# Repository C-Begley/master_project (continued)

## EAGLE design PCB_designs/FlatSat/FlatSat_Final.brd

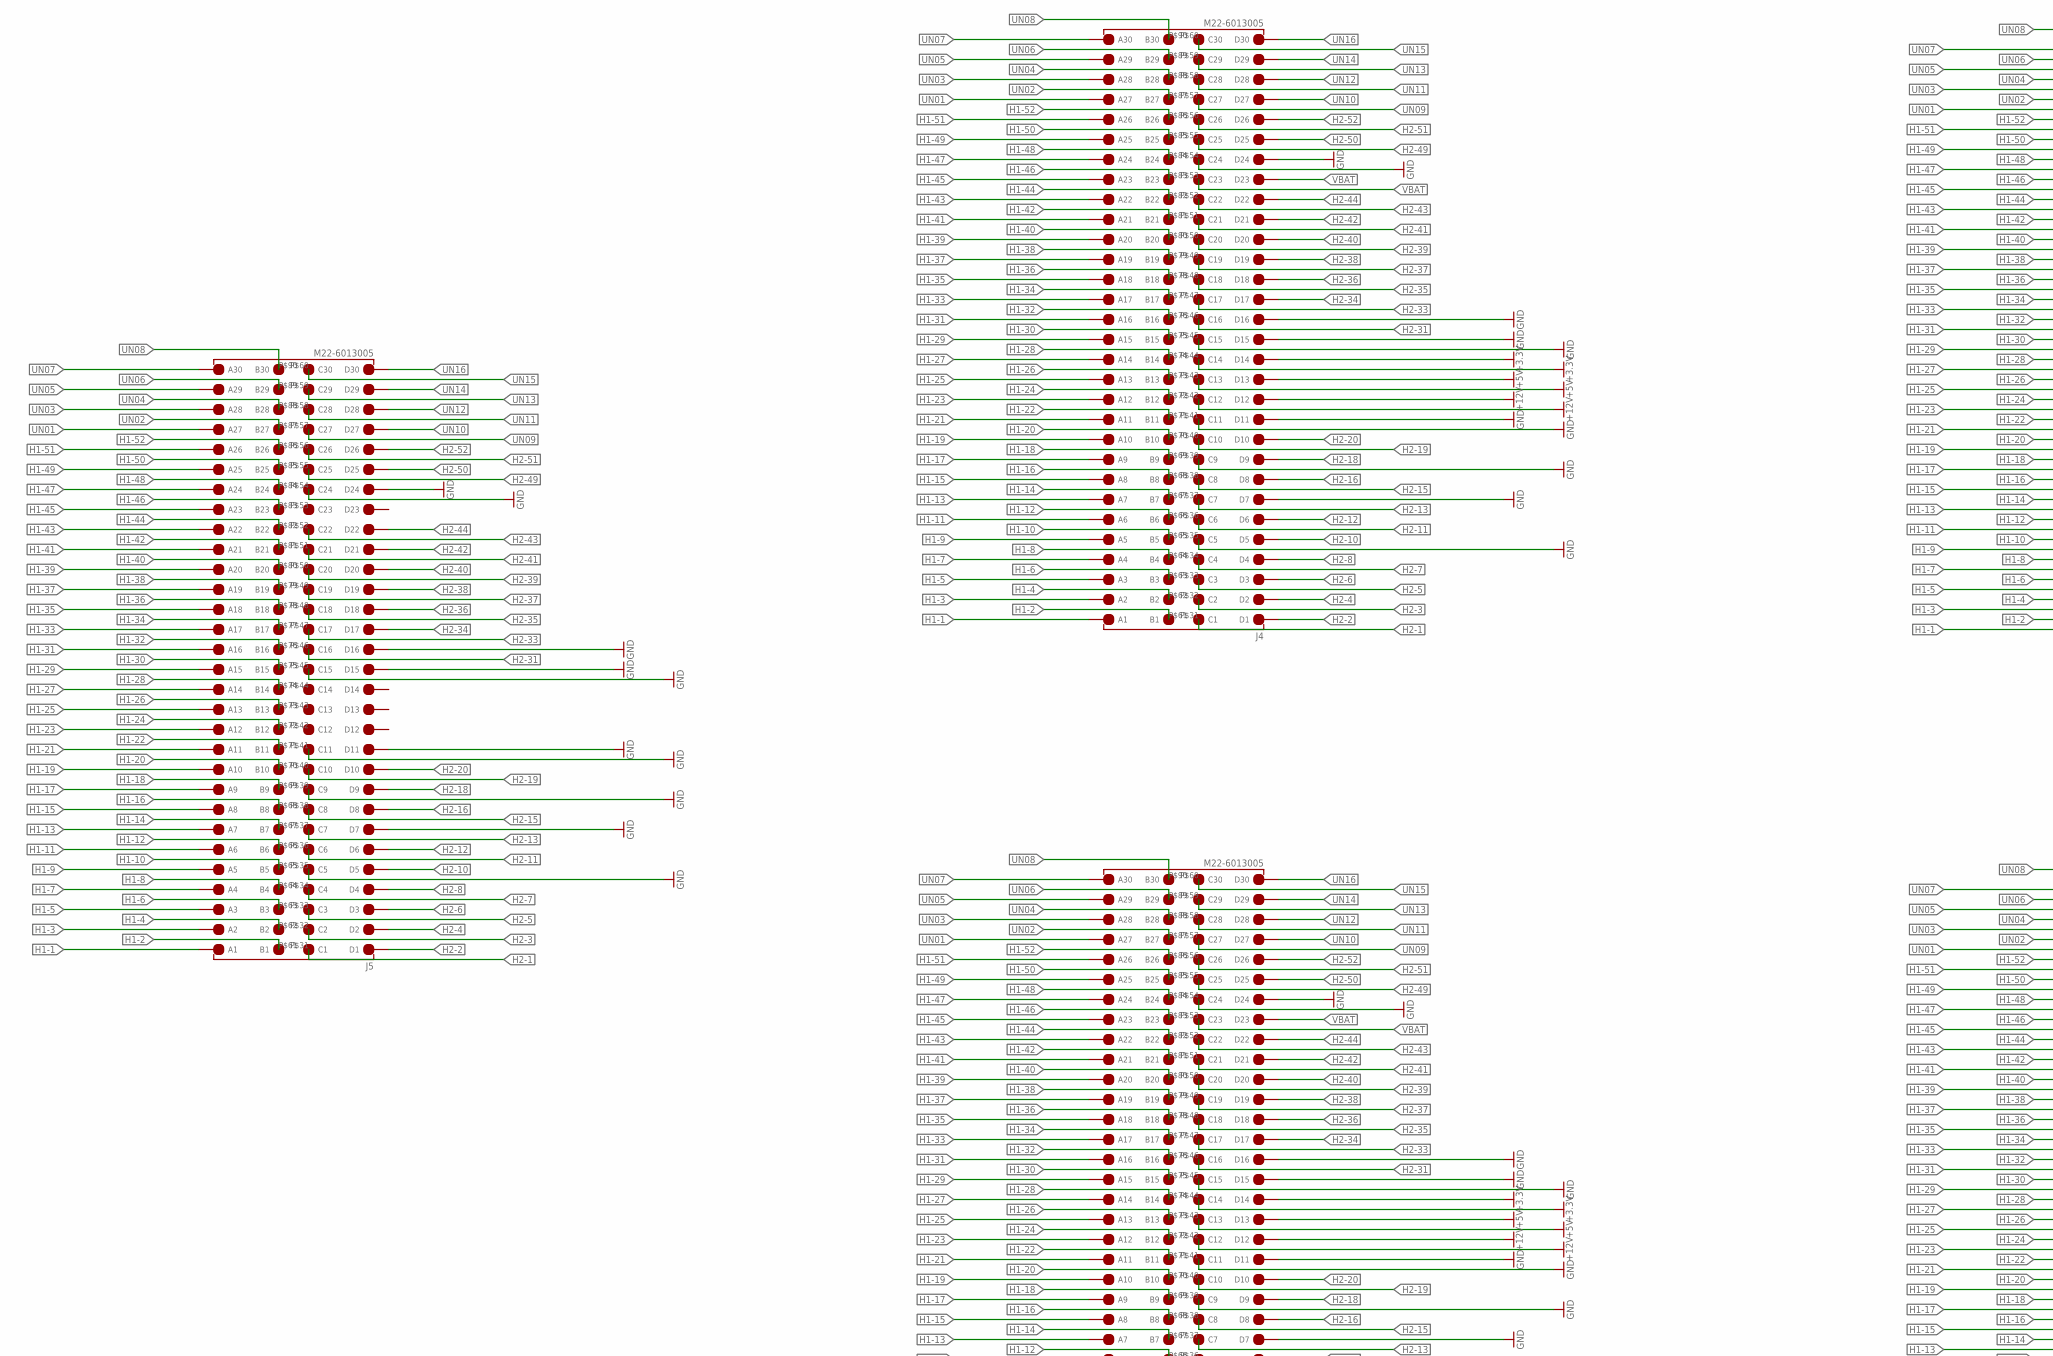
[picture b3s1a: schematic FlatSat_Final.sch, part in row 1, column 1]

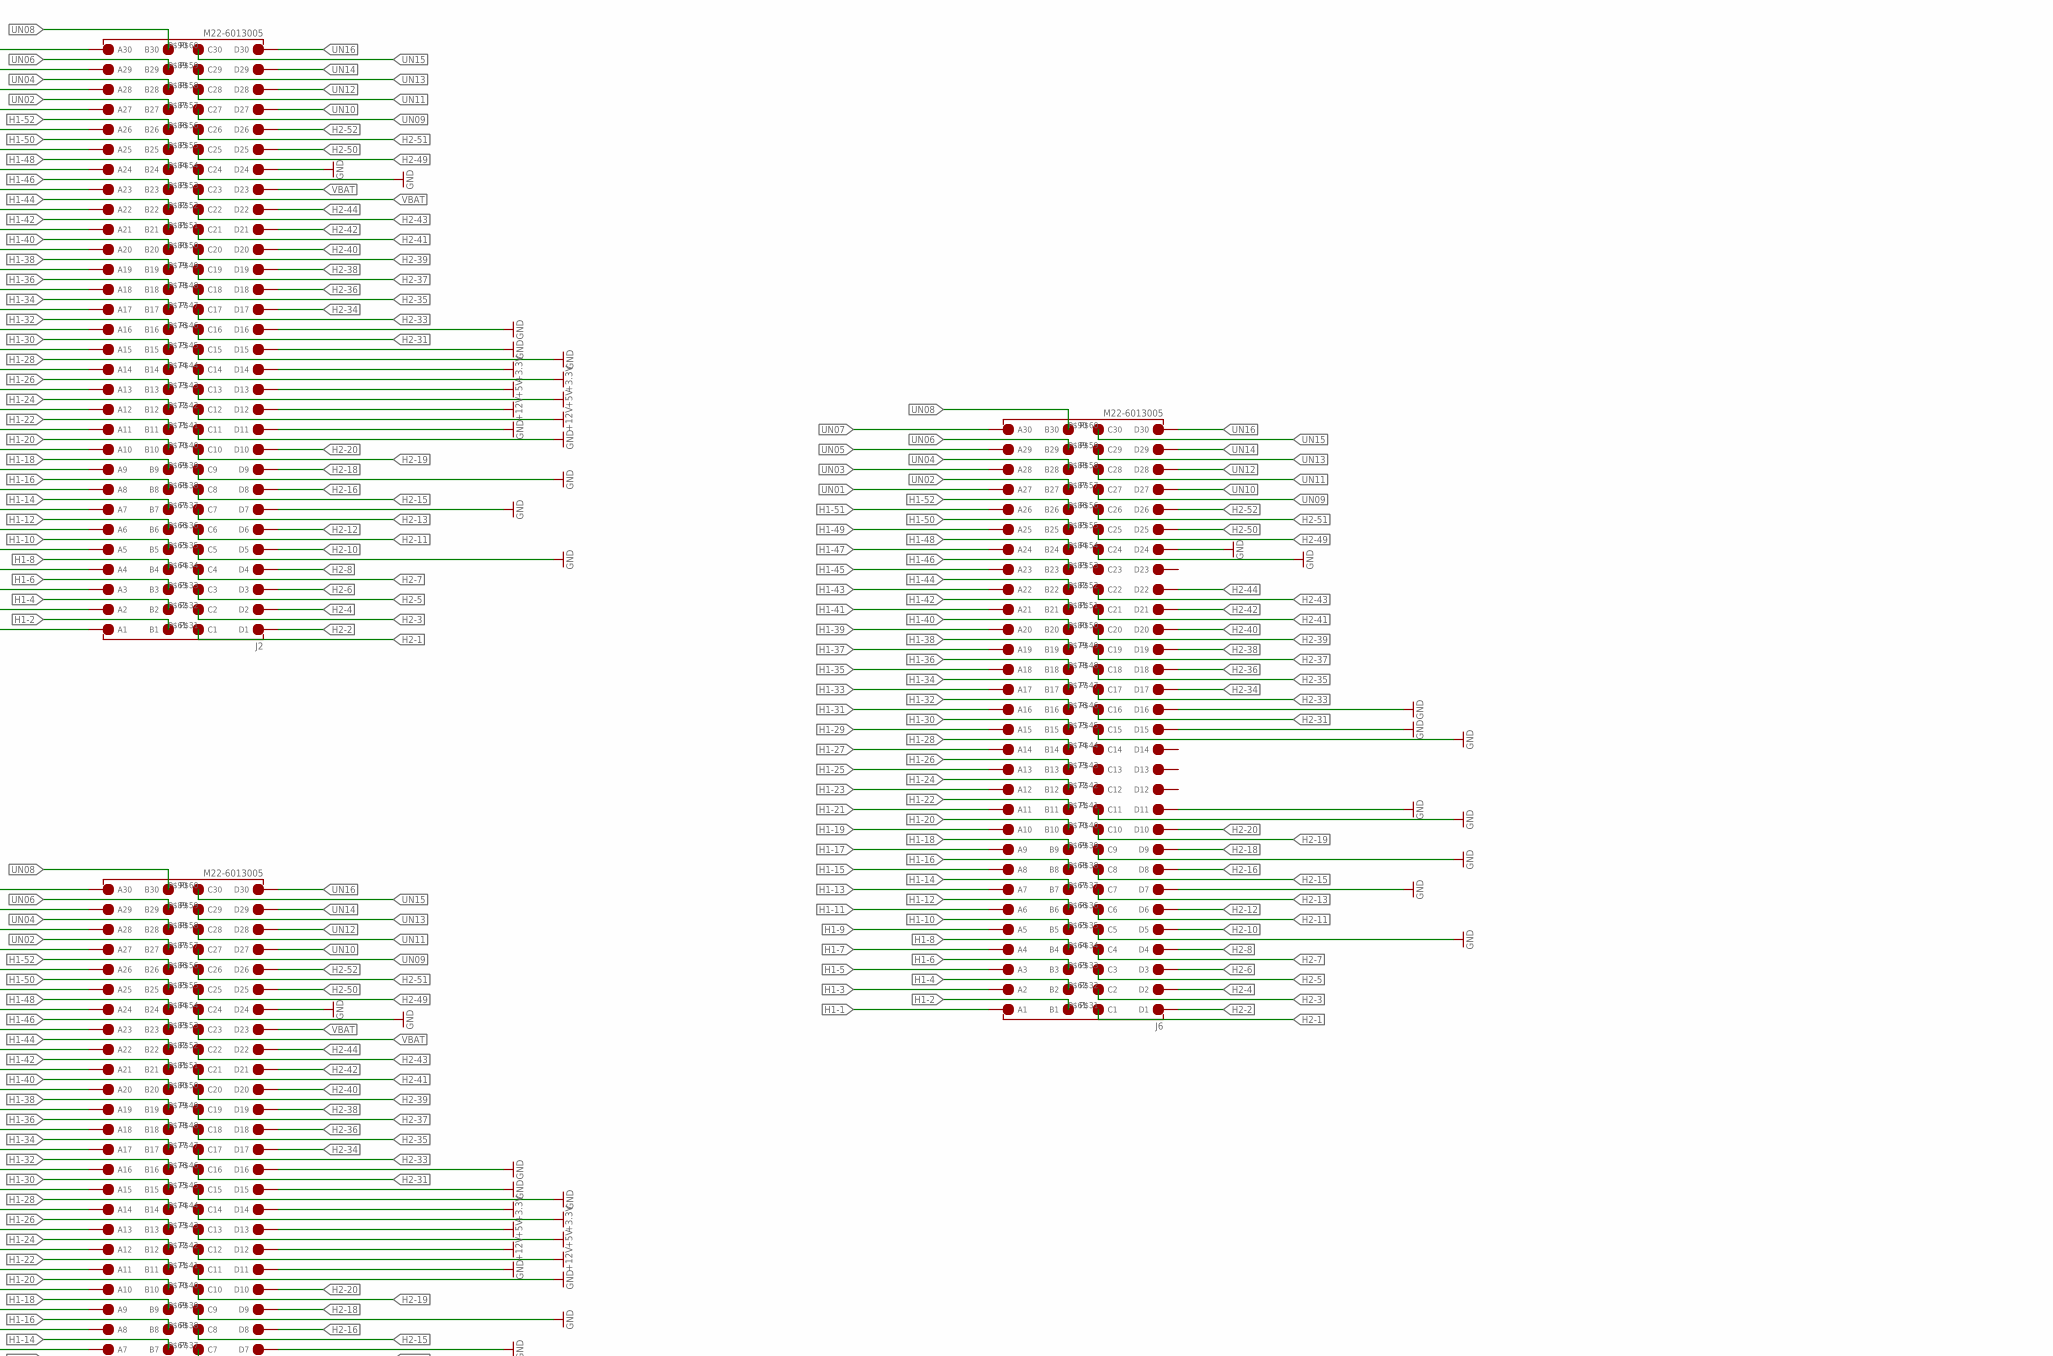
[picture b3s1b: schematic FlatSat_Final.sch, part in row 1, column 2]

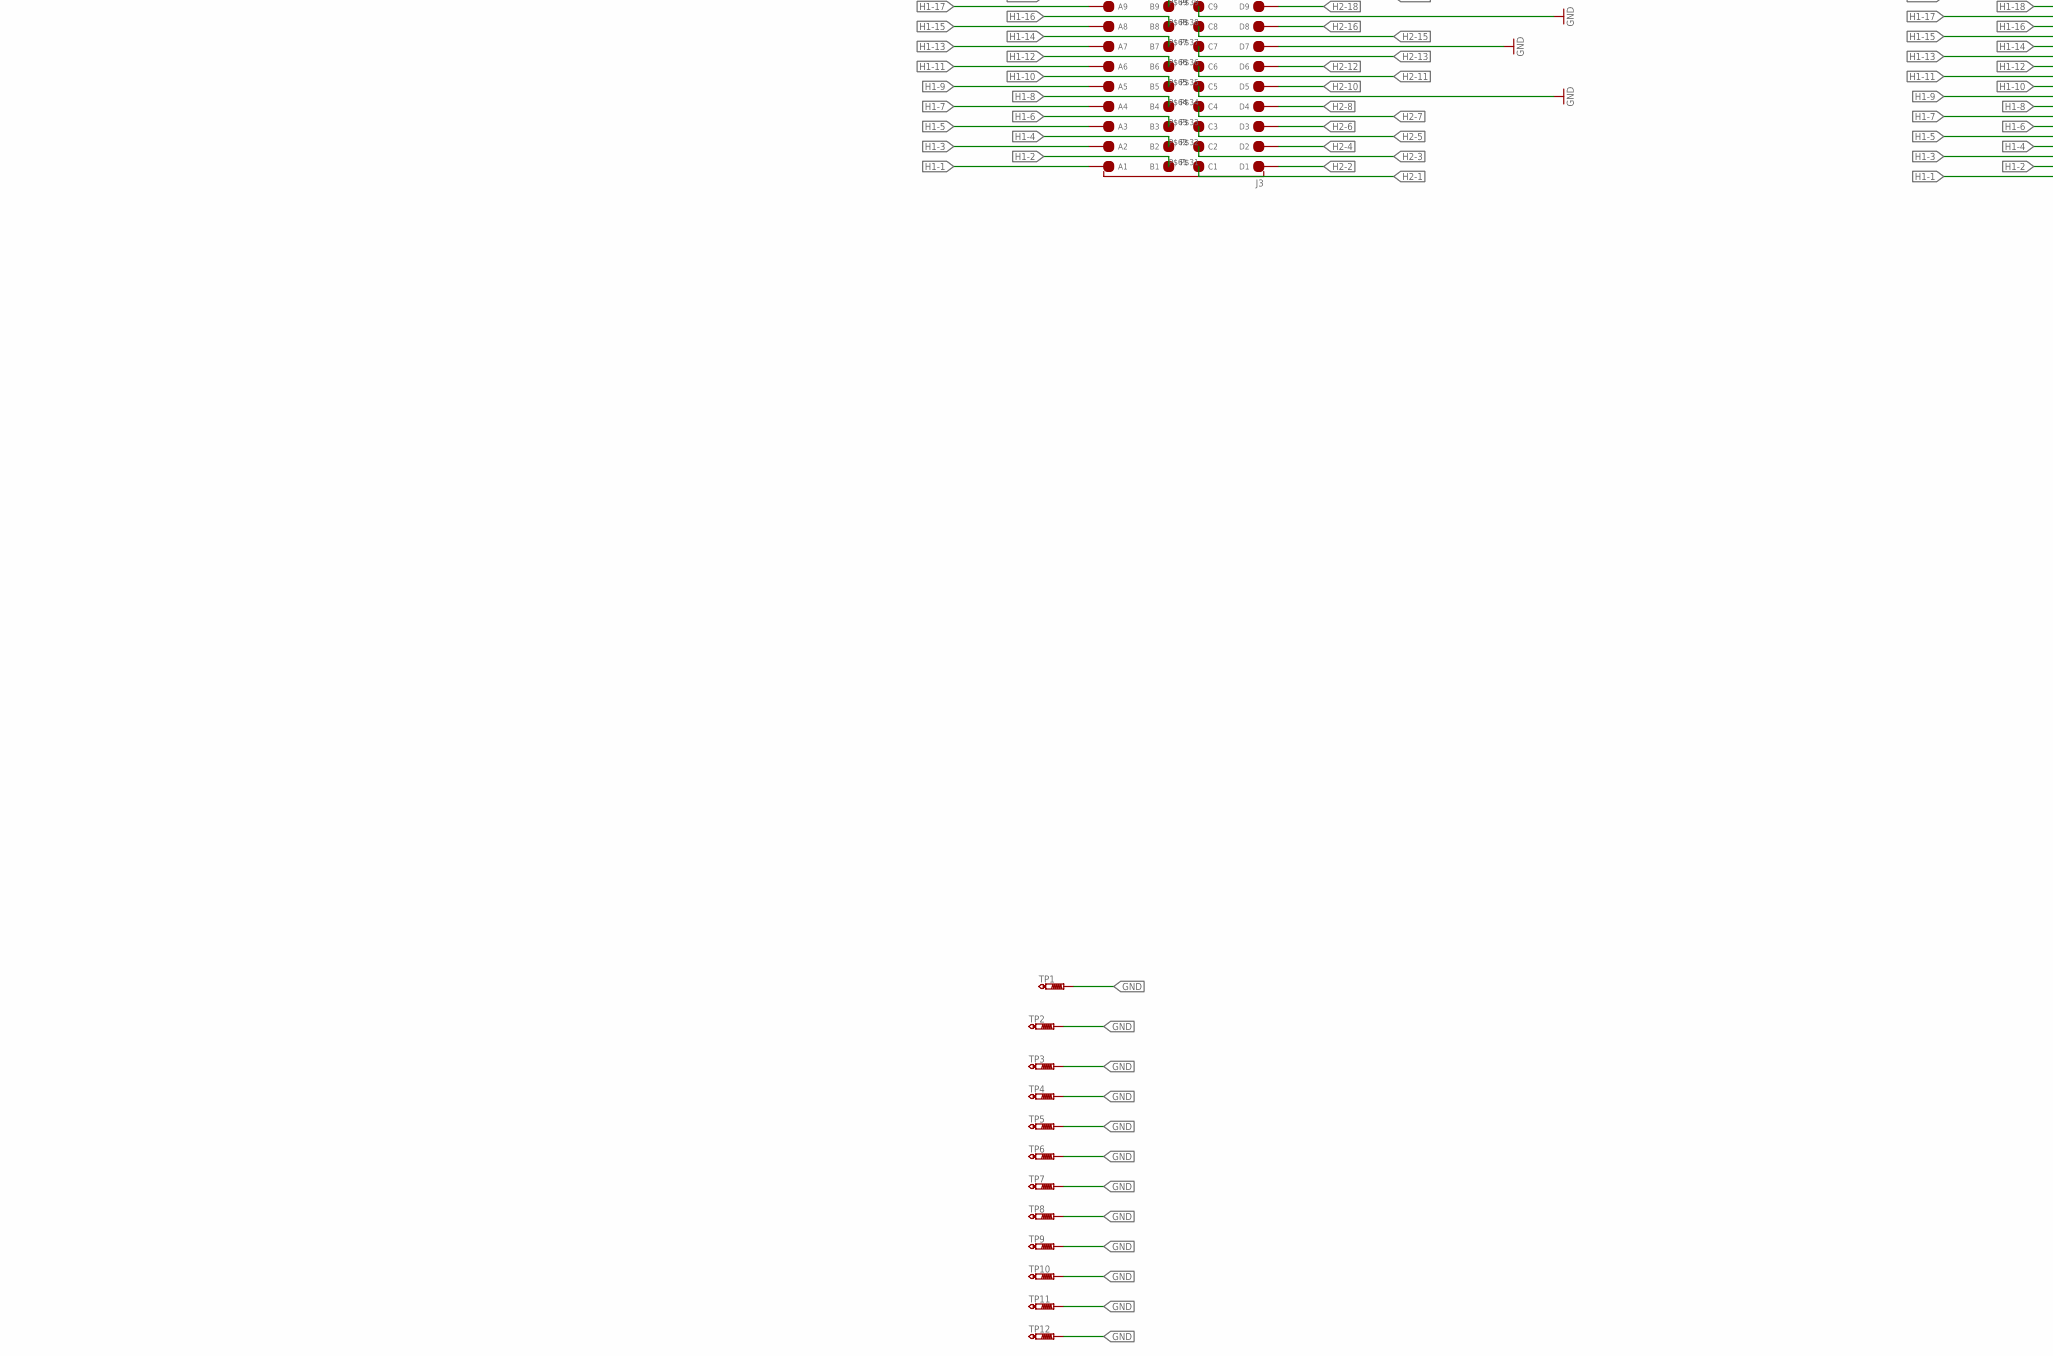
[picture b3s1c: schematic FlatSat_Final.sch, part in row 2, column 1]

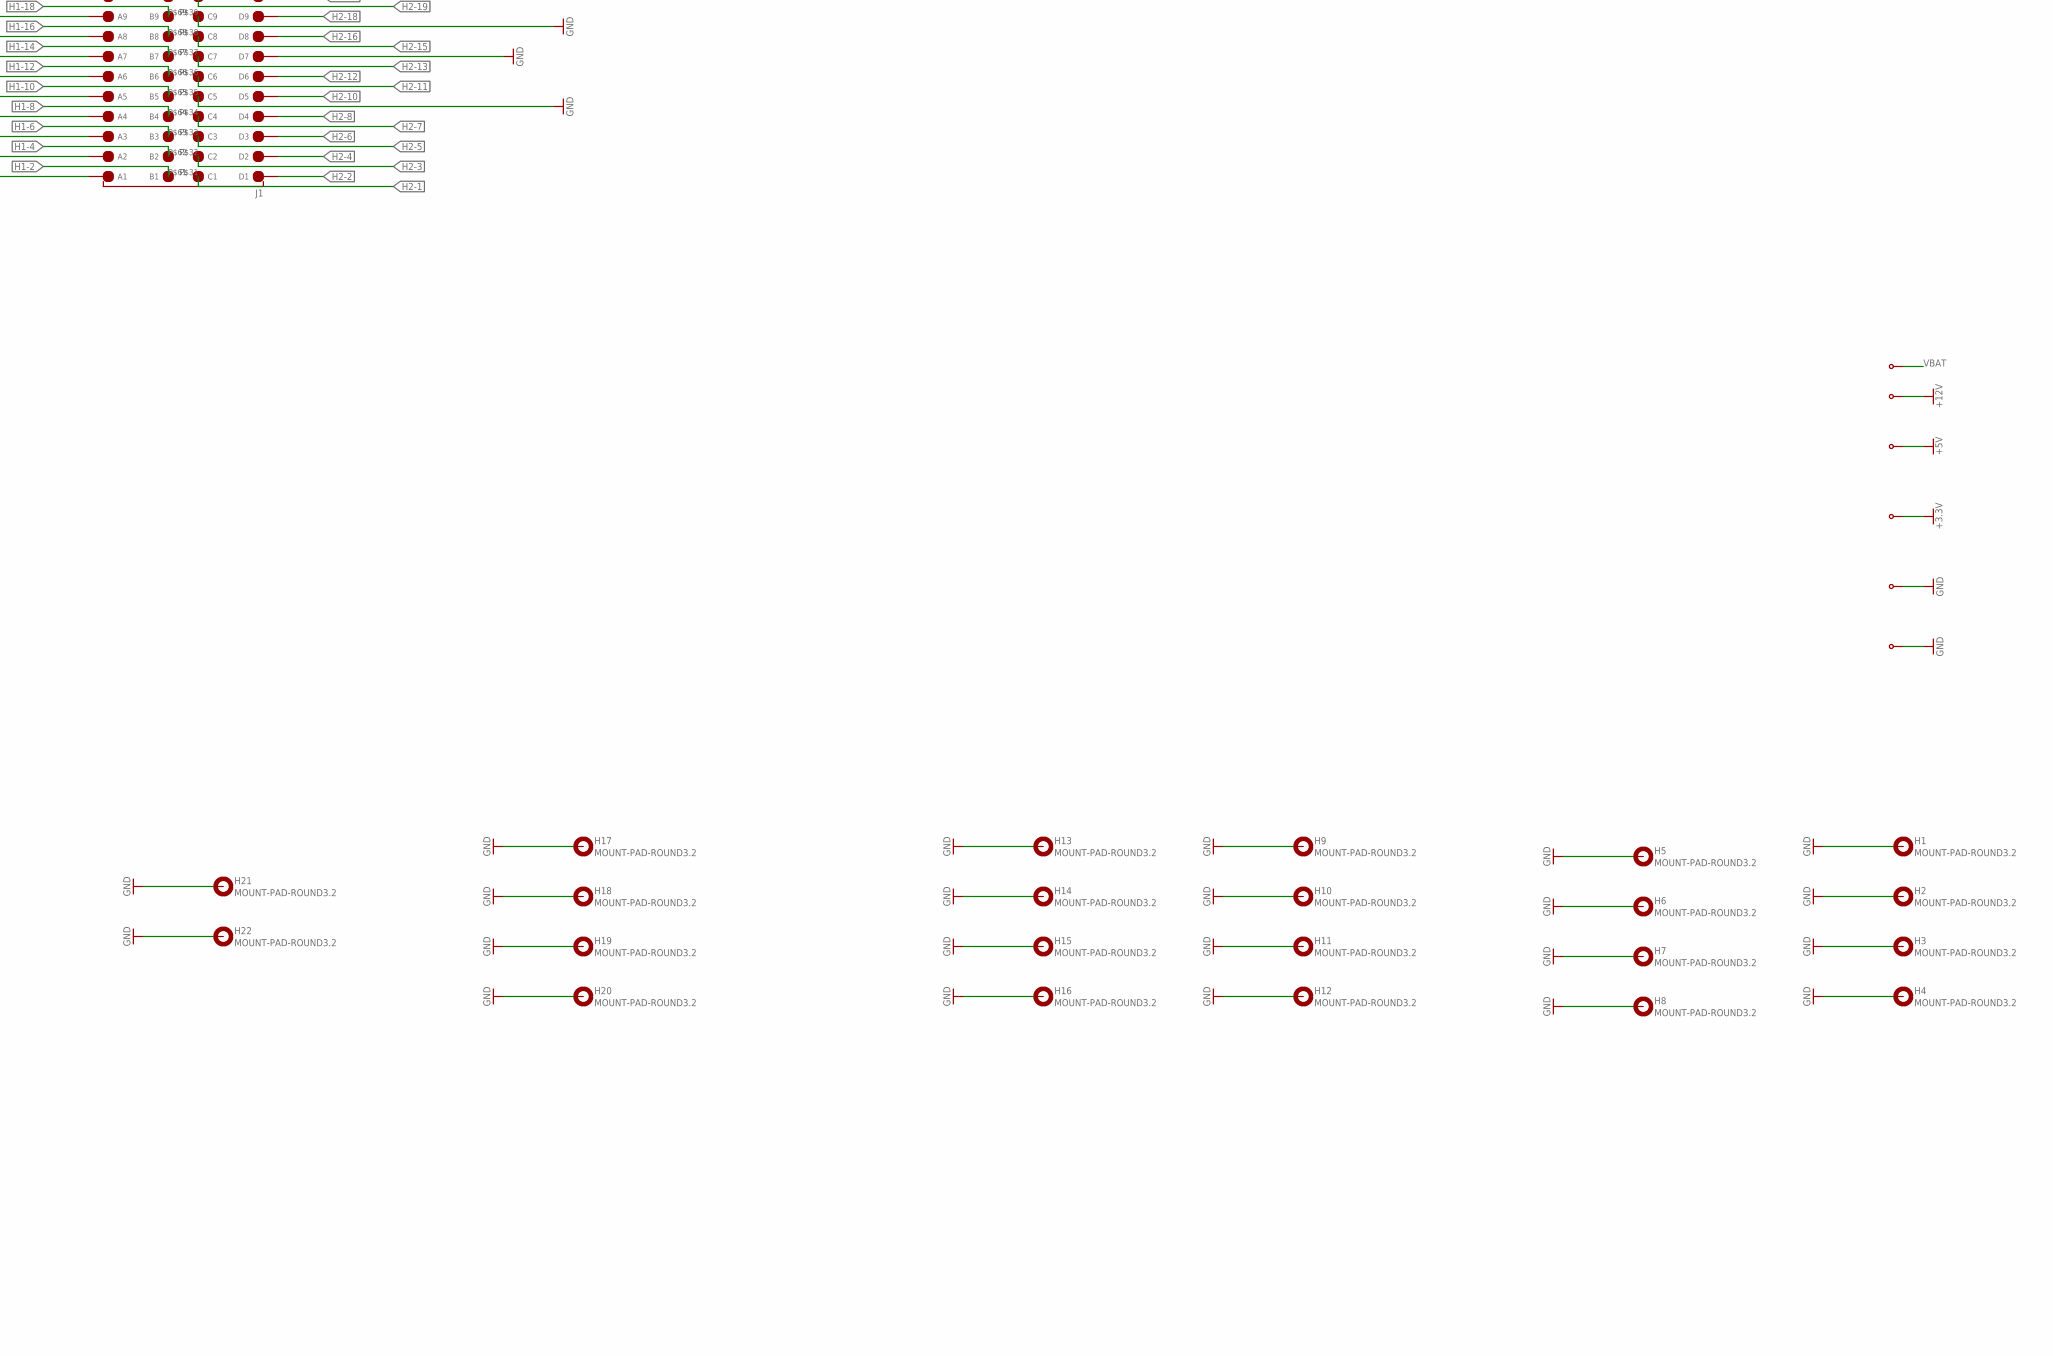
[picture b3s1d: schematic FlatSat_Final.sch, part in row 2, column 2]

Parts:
H1, H2, H3, H4, H5, H6, H7, H8, H9, H10, H11, H12, H13, H14, H15, H16, H17, H18, H19, H20, H21, H22: MOUNT-PAD-ROUND3.2; 3,2-PAD
J1, J2, J3, J4, J5, J6: M22-6013005; RHDR120W55P200_4X30_6020X820X9
TP1, TP2, TP3, TP4, TP5, TP6, TP7, TP8, TP9, TP10, TP11, TP12: PTR1PAD1-13; P1-13
U$1, U$2, U$3, U$4, U$5, U$6: BANANA-JACK; BANANA-PRINT

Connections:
+3.3V: J1.P$14 (D14), J1.P$44 (C14), J2.P$14 (D14), J2.P$44 (C14), J3.P$14 (D14), J3.P$44 (C14), J4.P$14 (D14), J4.P$44 (C14), U$3.P$1
+5V: J1.P$13 (D13), J1.P$43 (C13), J2.P$13 (D13), J2.P$43 (C13), J3.P$13 (D13), J3.P$43 (C13), J4.P$13 (D13), J4.P$43 (C13), U$2.P$1
+12V: J1.P$12 (D12), J1.P$42 (C12), J2.P$12 (D12), J2.P$42 (C12), J3.P$12 (D12), J3.P$42 (C12), J4.P$12 (D12), J4.P$42 (C12), U$1.P$1
GND: H1.B3,2, H2.B3,2, H3.B3,2, H4.B3,2, H5.B3,2, H6.B3,2, H7.B3,2, H8.B3,2, H9.B3,2, H10.B3,2, H11.B3,2, H12.B3,2, H13.B3,2, H14.B3,2, H15.B3,2, H16.B3,2, H17.B3,2, H18.B3,2, H19.B3,2, H20.B3,2, H21.B3,2, H22.B3,2, J1.P$7 (D7), J1.P$11 (D11), J1.P$15 (D15), J1.P$16 (D16), J1.P$24 (D24), J1.P$35 (C5), J1.P$39 (C9), J1.P$41 (C11), J1.P$45 (C15), J1.P$54 (C24), J2.P$7 (D7), J2.P$11 (D11), J2.P$15 (D15), J2.P$16 (D16), J2.P$24 (D24), J2.P$35 (C5), J2.P$39 (C9), J2.P$41 (C11), J2.P$45 (C15), J2.P$54 (C24), J3.P$7 (D7), J3.P$11 (D11), J3.P$15 (D15), J3.P$16 (D16), J3.P$24 (D24), J3.P$35 (C5), J3.P$39 (C9), J3.P$41 (C11), J3.P$45 (C15), J3.P$54 (C24), J4.P$7 (D7), J4.P$11 (D11), J4.P$15 (D15), J4.P$16 (D16), J4.P$24 (D24), J4.P$35 (C5), J4.P$39 (C9), J4.P$41 (C11), J4.P$45 (C15), J4.P$54 (C24), J5.P$7 (D7), J5.P$11 (D11), J5.P$15 (D15), J5.P$16 (D16), J5.P$24 (D24), J5.P$35 (C5), J5.P$39 (C9), J5.P$41 (C11), J5.P$45 (C15), J5.P$54 (C24), J6.P$7 (D7), J6.P$11 (D11), J6.P$15 (D15), J6.P$16 (D16), J6.P$24 (D24), J6.P$35 (C5), J6.P$39 (C9), J6.P$41 (C11), J6.P$45 (C15), J6.P$54 (C24), TP1.TP, TP2.TP, TP3.TP, TP4.TP, TP5.TP, TP6.TP, TP7.TP, TP8.TP, TP9.TP, TP10.TP, TP11.TP, TP12.TP, U$4.P$1, U$5.P$1
H1-1: J1.P$91 (A1), J2.P$91 (A1), J3.P$91 (A1), J4.P$91 (A1), J5.P$91 (A1), J6.P$91 (A1)
H1-2: J1.P$61 (B1), J2.P$61 (B1), J3.P$61 (B1), J4.P$61 (B1), J5.P$61 (B1), J6.P$61 (B1)
H1-3: J1.P$92 (A2), J2.P$92 (A2), J3.P$92 (A2), J4.P$92 (A2), J5.P$92 (A2), J6.P$92 (A2)
H1-4: J1.P$62 (B2), J2.P$62 (B2), J3.P$62 (B2), J4.P$62 (B2), J5.P$62 (B2), J6.P$62 (B2)
H1-5: J1.P$93 (A3), J2.P$93 (A3), J3.P$93 (A3), J4.P$93 (A3), J5.P$93 (A3), J6.P$93 (A3)
H1-6: J1.P$63 (B3), J2.P$63 (B3), J3.P$63 (B3), J4.P$63 (B3), J5.P$63 (B3), J6.P$63 (B3)
H1-7: J1.P$94 (A4), J2.P$94 (A4), J3.P$94 (A4), J4.P$94 (A4), J5.P$94 (A4), J6.P$94 (A4)
H1-8: J1.P$64 (B4), J2.P$64 (B4), J3.P$64 (B4), J4.P$64 (B4), J5.P$64 (B4), J6.P$64 (B4)
H1-9: J1.P$95 (A5), J2.P$95 (A5), J3.P$95 (A5), J4.P$95 (A5), J5.P$95 (A5), J6.P$95 (A5)
H1-10: J1.P$65 (B5), J2.P$65 (B5), J3.P$65 (B5), J4.P$65 (B5), J5.P$65 (B5), J6.P$65 (B5)
H1-11: J1.P$96 (A6), J2.P$96 (A6), J3.P$96 (A6), J4.P$96 (A6), J5.P$96 (A6), J6.P$96 (A6)
H1-12: J1.P$66 (B6), J2.P$66 (B6), J3.P$66 (B6), J4.P$66 (B6), J5.P$66 (B6), J6.P$66 (B6)
H1-13: J1.P$97 (A7), J2.P$97 (A7), J3.P$97 (A7), J4.P$97 (A7), J5.P$97 (A7), J6.P$97 (A7)
H1-14: J1.P$67 (B7), J2.P$67 (B7), J3.P$67 (B7), J4.P$67 (B7), J5.P$67 (B7), J6.P$67 (B7)
H1-15: J1.P$98 (A8), J2.P$98 (A8), J3.P$98 (A8), J4.P$98 (A8), J5.P$98 (A8), J6.P$98 (A8)
H1-16: J1.P$68 (B8), J2.P$68 (B8), J3.P$68 (B8), J4.P$68 (B8), J5.P$68 (B8), J6.P$68 (B8)
H1-17: J1.P$99 (A9), J2.P$99 (A9), J3.P$99 (A9), J4.P$99 (A9), J5.P$99 (A9), J6.P$99 (A9)
H1-18: J1.P$69 (B9), J2.P$69 (B9), J3.P$69 (B9), J4.P$69 (B9), J5.P$69 (B9), J6.P$69 (B9)
H1-19: J1.P$100 (A10), J2.P$100 (A10), J3.P$100 (A10), J4.P$100 (A10), J5.P$100 (A10), J6.P$100 (A10)
H1-20: J1.P$70 (B10), J2.P$70 (B10), J3.P$70 (B10), J4.P$70 (B10), J5.P$70 (B10), J6.P$70 (B10)
H1-21: J1.P$101 (A11), J2.P$101 (A11), J3.P$101 (A11), J4.P$101 (A11), J5.P$101 (A11), J6.P$101 (A11)
H1-22: J1.P$71 (B11), J2.P$71 (B11), J3.P$71 (B11), J4.P$71 (B11), J5.P$71 (B11), J6.P$71 (B11)
H1-23: J1.P$102 (A12), J2.P$102 (A12), J3.P$102 (A12), J4.P$102 (A12), J5.P$102 (A12), J6.P$102 (A12)
H1-24: J1.P$72 (B12), J2.P$72 (B12), J3.P$72 (B12), J4.P$72 (B12), J5.P$72 (B12), J6.P$72 (B12)
H1-25: J1.P$103 (A13), J2.P$103 (A13), J3.P$103 (A13), J4.P$103 (A13), J5.P$103 (A13), J6.P$103 (A13)
H1-26: J1.P$73 (B13), J2.P$73 (B13), J3.P$73 (B13), J4.P$73 (B13), J5.P$73 (B13), J6.P$73 (B13)
H1-27: J1.P$104 (A14), J2.P$104 (A14), J3.P$104 (A14), J4.P$104 (A14), J5.P$104 (A14), J6.P$104 (A14)
H1-28: J1.P$74 (B14), J2.P$74 (B14), J3.P$74 (B14), J4.P$74 (B14), J5.P$74 (B14), J6.P$74 (B14)
H1-29: J1.P$105 (A15), J2.P$105 (A15), J3.P$105 (A15), J4.P$105 (A15), J5.P$105 (A15), J6.P$105 (A15)
H1-30: J1.P$75 (B15), J2.P$75 (B15), J3.P$75 (B15), J4.P$75 (B15), J5.P$75 (B15), J6.P$75 (B15)
H1-31: J1.P$106 (A16), J2.P$106 (A16), J3.P$106 (A16), J4.P$106 (A16), J5.P$106 (A16), J6.P$106 (A16)
H1-32: J1.P$76 (B16), J2.P$76 (B16), J3.P$76 (B16), J4.P$76 (B16), J5.P$76 (B16), J6.P$76 (B16)
H1-33: J1.P$107 (A17), J2.P$107 (A17), J3.P$107 (A17), J4.P$107 (A17), J5.P$107 (A17), J6.P$107 (A17)
H1-34: J1.P$77 (B17), J2.P$77 (B17), J3.P$77 (B17), J4.P$77 (B17), J5.P$77 (B17), J6.P$77 (B17)
H1-35: J1.P$108 (A18), J2.P$108 (A18), J3.P$108 (A18), J4.P$108 (A18), J5.P$108 (A18), J6.P$108 (A18)
H1-36: J1.P$78 (B18), J2.P$78 (B18), J3.P$78 (B18), J4.P$78 (B18), J5.P$78 (B18), J6.P$78 (B18)
H1-37: J1.P$109 (A19), J2.P$109 (A19), J3.P$109 (A19), J4.P$109 (A19), J5.P$109 (A19), J6.P$109 (A19)
H1-38: J1.P$79 (B19), J2.P$79 (B19), J3.P$79 (B19), J4.P$79 (B19), J5.P$79 (B19), J6.P$79 (B19)
H1-39: J1.P$110 (A20), J2.P$110 (A20), J3.P$110 (A20), J4.P$110 (A20), J5.P$110 (A20), J6.P$110 (A20)
H1-40: J1.P$80 (B20), J2.P$80 (B20), J3.P$80 (B20), J4.P$80 (B20), J5.P$80 (B20), J6.P$80 (B20)
H1-41: J1.P$111 (A21), J2.P$111 (A21), J3.P$111 (A21), J4.P$111 (A21), J5.P$111 (A21), J6.P$111 (A21)
H1-42: J1.P$81 (B21), J2.P$81 (B21), J3.P$81 (B21), J4.P$81 (B21), J5.P$81 (B21), J6.P$81 (B21)
H1-43: J1.P$112 (A22), J2.P$112 (A22), J3.P$112 (A22), J4.P$112 (A22), J5.P$112 (A22), J6.P$112 (A22)
H1-44: J1.P$82 (B22), J2.P$82 (B22), J3.P$82 (B22), J4.P$82 (B22), J5.P$82 (B22), J6.P$82 (B22)
H1-45: J1.P$113 (A23), J2.P$113 (A23), J3.P$113 (A23), J4.P$113 (A23), J5.P$113 (A23), J6.P$113 (A23)
H1-46: J1.P$83 (B23), J2.P$83 (B23), J3.P$83 (B23), J4.P$83 (B23), J5.P$83 (B23), J6.P$83 (B23)
H1-47: J1.P$114 (A24), J2.P$114 (A24), J3.P$114 (A24), J4.P$114 (A24), J5.P$114 (A24), J6.P$114 (A24)
H1-48: J1.P$84 (B24), J2.P$84 (B24), J3.P$84 (B24), J4.P$84 (B24), J5.P$84 (B24), J6.P$84 (B24)
H1-49: J1.P$115 (A25), J2.P$115 (A25), J3.P$115 (A25), J4.P$115 (A25), J5.P$115 (A25), J6.P$115 (A25)
H1-50: J1.P$85 (B25), J2.P$85 (B25), J3.P$85 (B25), J4.P$85 (B25), J5.P$85 (B25), J6.P$85 (B25)
H1-51: J1.P$116 (A26), J2.P$116 (A26), J3.P$116 (A26), J4.P$116 (A26), J5.P$116 (A26), J6.P$116 (A26)
H1-52: J1.P$86 (B26), J2.P$86 (B26), J3.P$86 (B26), J4.P$86 (B26), J5.P$86 (B26), J6.P$86 (B26)
H2-1: J1.P$31 (C1), J2.P$31 (C1), J3.P$31 (C1), J4.P$31 (C1), J5.P$31 (C1), J6.P$31 (C1)
H2-2: J1.P$1 (D1), J2.P$1 (D1), J3.P$1 (D1), J4.P$1 (D1), J5.P$1 (D1), J6.P$1 (D1)
H2-3: J1.P$32 (C2), J2.P$32 (C2), J3.P$32 (C2), J4.P$32 (C2), J5.P$32 (C2), J6.P$32 (C2)
H2-4: J1.P$2 (D2), J2.P$2 (D2), J3.P$2 (D2), J4.P$2 (D2), J5.P$2 (D2), J6.P$2 (D2)
H2-5: J1.P$33 (C3), J2.P$33 (C3), J3.P$33 (C3), J4.P$33 (C3), J5.P$33 (C3), J6.P$33 (C3)
H2-6: J1.P$3 (D3), J2.P$3 (D3), J3.P$3 (D3), J4.P$3 (D3), J5.P$3 (D3), J6.P$3 (D3)
H2-7: J1.P$34 (C4), J2.P$34 (C4), J3.P$34 (C4), J4.P$34 (C4), J5.P$34 (C4), J6.P$34 (C4)
H2-8: J1.P$4 (D4), J2.P$4 (D4), J3.P$4 (D4), J4.P$4 (D4), J5.P$4 (D4), J6.P$4 (D4)
H2-10: J1.P$5 (D5), J2.P$5 (D5), J3.P$5 (D5), J4.P$5 (D5), J5.P$5 (D5), J6.P$5 (D5)
H2-11: J1.P$36 (C6), J2.P$36 (C6), J3.P$36 (C6), J4.P$36 (C6), J5.P$36 (C6), J6.P$36 (C6)
H2-12: J1.P$6 (D6), J2.P$6 (D6), J3.P$6 (D6), J4.P$6 (D6), J5.P$6 (D6), J6.P$6 (D6)
H2-13: J1.P$37 (C7), J2.P$37 (C7), J3.P$37 (C7), J4.P$37 (C7), J5.P$37 (C7), J6.P$37 (C7)
H2-15: J1.P$38 (C8), J2.P$38 (C8), J3.P$38 (C8), J4.P$38 (C8), J5.P$38 (C8), J6.P$38 (C8)
H2-16: J1.P$8 (D8), J2.P$8 (D8), J3.P$8 (D8), J4.P$8 (D8), J5.P$8 (D8), J6.P$8 (D8)
H2-18: J1.P$9 (D9), J2.P$9 (D9), J3.P$9 (D9), J4.P$9 (D9), J5.P$9 (D9), J6.P$9 (D9)
H2-19: J1.P$40 (C10), J2.P$40 (C10), J3.P$40 (C10), J4.P$40 (C10), J5.P$40 (C10), J6.P$40 (C10)
H2-20: J1.P$10 (D10), J2.P$10 (D10), J3.P$10 (D10), J4.P$10 (D10), J5.P$10 (D10), J6.P$10 (D10)
H2-31: J1.P$46 (C16), J2.P$46 (C16), J3.P$46 (C16), J4.P$46 (C16), J5.P$46 (C16), J6.P$46 (C16)
H2-33: J1.P$47 (C17), J2.P$47 (C17), J3.P$47 (C17), J4.P$47 (C17), J5.P$47 (C17), J6.P$47 (C17)
H2-34: J1.P$17 (D17), J2.P$17 (D17), J3.P$17 (D17), J4.P$17 (D17), J5.P$17 (D17), J6.P$17 (D17)
H2-35: J1.P$48 (C18), J2.P$48 (C18), J3.P$48 (C18), J4.P$48 (C18), J5.P$48 (C18), J6.P$48 (C18)
H2-36: J1.P$18 (D18), J2.P$18 (D18), J3.P$18 (D18), J4.P$18 (D18), J5.P$18 (D18), J6.P$18 (D18)
H2-37: J1.P$49 (C19), J2.P$49 (C19), J3.P$49 (C19), J4.P$49 (C19), J5.P$49 (C19), J6.P$49 (C19)
H2-38: J1.P$19 (D19), J2.P$19 (D19), J3.P$19 (D19), J4.P$19 (D19), J5.P$19 (D19), J6.P$19 (D19)
H2-39: J1.P$50 (C20), J2.P$50 (C20), J3.P$50 (C20), J4.P$50 (C20), J5.P$50 (C20), J6.P$50 (C20)
H2-40: J1.P$20 (D20), J2.P$20 (D20), J3.P$20 (D20), J4.P$20 (D20), J5.P$20 (D20), J6.P$20 (D20)
H2-41: J1.P$51 (C21), J2.P$51 (C21), J3.P$51 (C21), J4.P$51 (C21), J5.P$51 (C21), J6.P$51 (C21)
H2-42: J1.P$21 (D21), J2.P$21 (D21), J3.P$21 (D21), J4.P$21 (D21), J5.P$21 (D21), J6.P$21 (D21)
H2-43: J1.P$52 (C22), J2.P$52 (C22), J3.P$52 (C22), J4.P$52 (C22), J5.P$52 (C22), J6.P$52 (C22)
H2-44: J1.P$22 (D22), J2.P$22 (D22), J3.P$22 (D22), J4.P$22 (D22), J5.P$22 (D22), J6.P$22 (D22)
H2-49: J1.P$55 (C25), J2.P$55 (C25), J3.P$55 (C25), J4.P$55 (C25), J5.P$55 (C25), J6.P$55 (C25)
H2-50: J1.P$25 (D25), J2.P$25 (D25), J3.P$25 (D25), J4.P$25 (D25), J5.P$25 (D25), J6.P$25 (D25)
H2-51: J1.P$56 (C26), J2.P$56 (C26), J3.P$56 (C26), J4.P$56 (C26), J5.P$56 (C26), J6.P$56 (C26)
H2-52: J1.P$26 (D26), J2.P$26 (D26), J3.P$26 (D26), J4.P$26 (D26), J5.P$26 (D26), J6.P$26 (D26)
UN01: J1.P$117 (A27), J2.P$117 (A27), J3.P$117 (A27), J4.P$117 (A27), J5.P$117 (A27), J6.P$117 (A27)
UN02: J1.P$87 (B27), J2.P$87 (B27), J3.P$87 (B27), J4.P$87 (B27), J5.P$87 (B27), J6.P$87 (B27)
UN03: J1.P$118 (A28), J2.P$118 (A28), J3.P$118 (A28), J4.P$118 (A28), J5.P$118 (A28), J6.P$118 (A28)
UN04: J1.P$88 (B28), J2.P$88 (B28), J3.P$88 (B28), J4.P$88 (B28), J5.P$88 (B28), J6.P$88 (B28)
UN05: J1.P$119 (A29), J2.P$119 (A29), J3.P$119 (A29), J4.P$119 (A29), J5.P$119 (A29), J6.P$119 (A29)
UN06: J1.P$89 (B29), J2.P$89 (B29), J3.P$89 (B29), J4.P$89 (B29), J5.P$89 (B29), J6.P$89 (B29)
UN07: J1.P$120 (A30), J2.P$120 (A30), J3.P$120 (A30), J4.P$120 (A30), J5.P$120 (A30), J6.P$120 (A30)
UN08: J1.P$90 (B30), J2.P$90 (B30), J3.P$90 (B30), J4.P$90 (B30), J5.P$90 (B30), J6.P$90 (B30)
UN09: J1.P$57 (C27), J2.P$57 (C27), J3.P$57 (C27), J4.P$57 (C27), J5.P$57 (C27), J6.P$57 (C27)
UN10: J1.P$27 (D27), J2.P$27 (D27), J3.P$27 (D27), J4.P$27 (D27), J5.P$27 (D27), J6.P$27 (D27)
UN11: J1.P$58 (C28), J2.P$58 (C28), J3.P$58 (C28), J4.P$58 (C28), J5.P$58 (C28), J6.P$58 (C28)
UN12: J1.P$28 (D28), J2.P$28 (D28), J3.P$28 (D28), J4.P$28 (D28), J5.P$28 (D28), J6.P$28 (D28)
UN13: J1.P$59 (C29), J2.P$59 (C29), J3.P$59 (C29), J4.P$59 (C29), J5.P$59 (C29), J6.P$59 (C29)
UN14: J1.P$29 (D29), J2.P$29 (D29), J3.P$29 (D29), J4.P$29 (D29), J5.P$29 (D29), J6.P$29 (D29)
UN15: J1.P$60 (C30), J2.P$60 (C30), J3.P$60 (C30), J4.P$60 (C30), J5.P$60 (C30), J6.P$60 (C30)
UN16: J1.P$30 (D30), J2.P$30 (D30), J3.P$30 (D30), J4.P$30 (D30), J5.P$30 (D30), J6.P$30 (D30)
VBAT: J1.P$23 (D23), J1.P$53 (C23), J2.P$23 (D23), J2.P$53 (C23), J3.P$23 (D23), J3.P$53 (C23), J4.P$23 (D23), J4.P$53 (C23), U$6.P$1

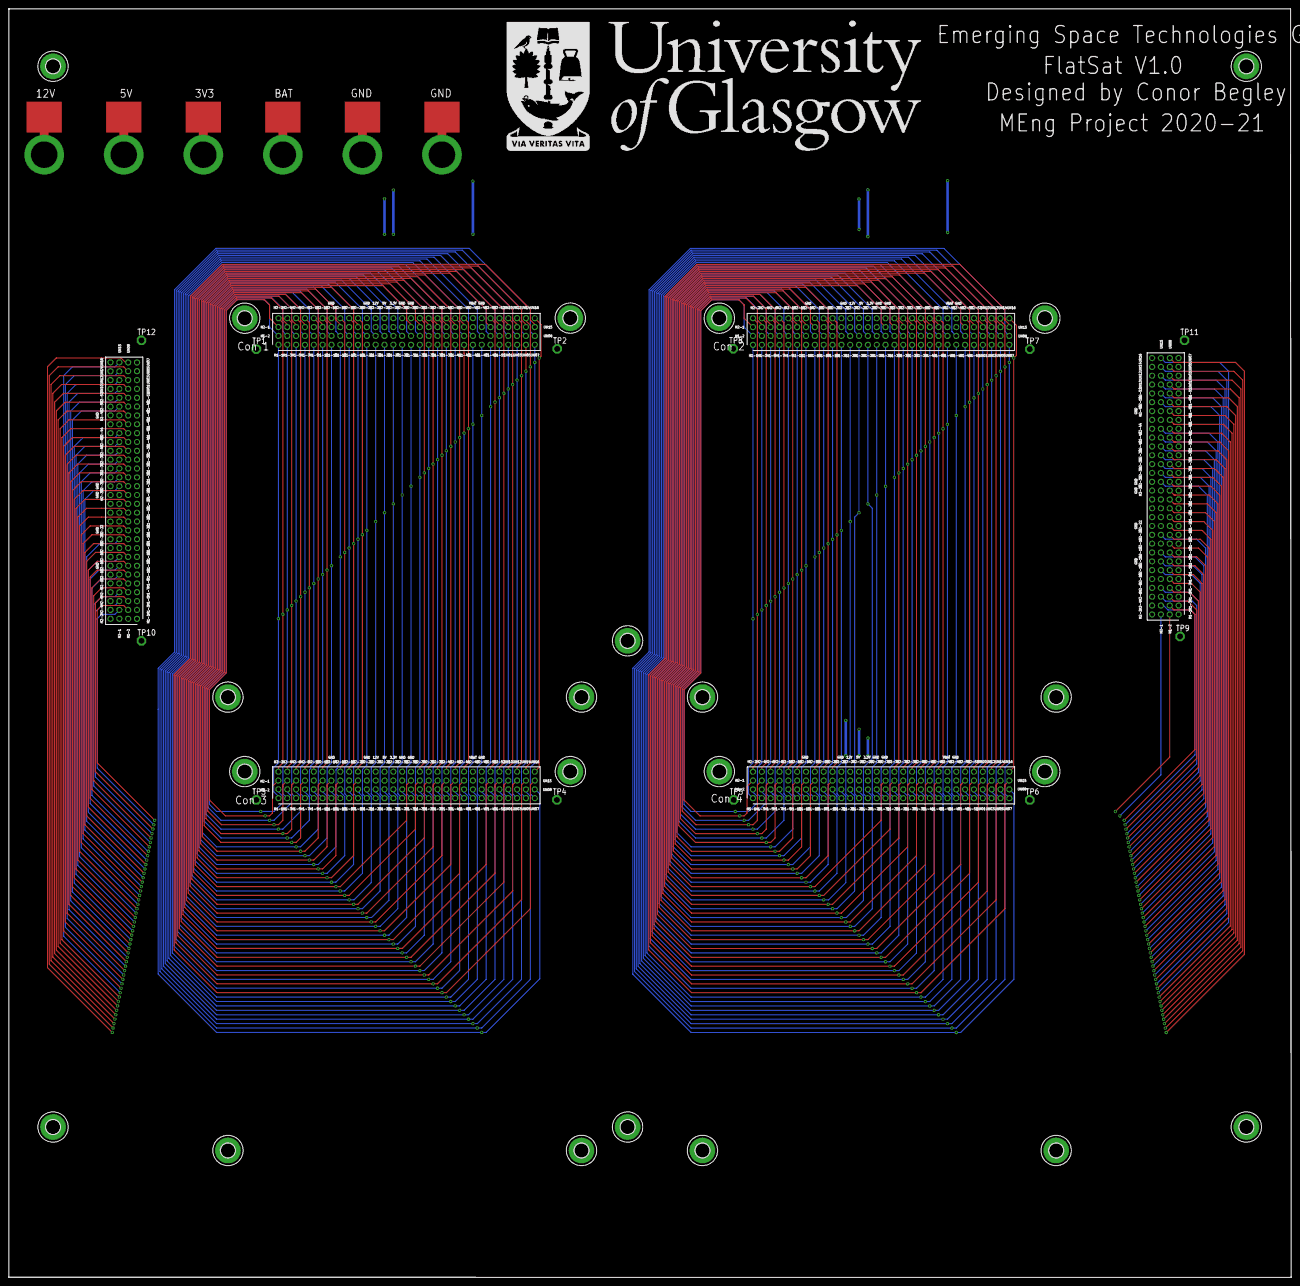
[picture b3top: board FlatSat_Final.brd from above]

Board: 4 copper layers, 290.1 x 287.0 mm, 46 parts (0 on the bottom side), 107 nets.

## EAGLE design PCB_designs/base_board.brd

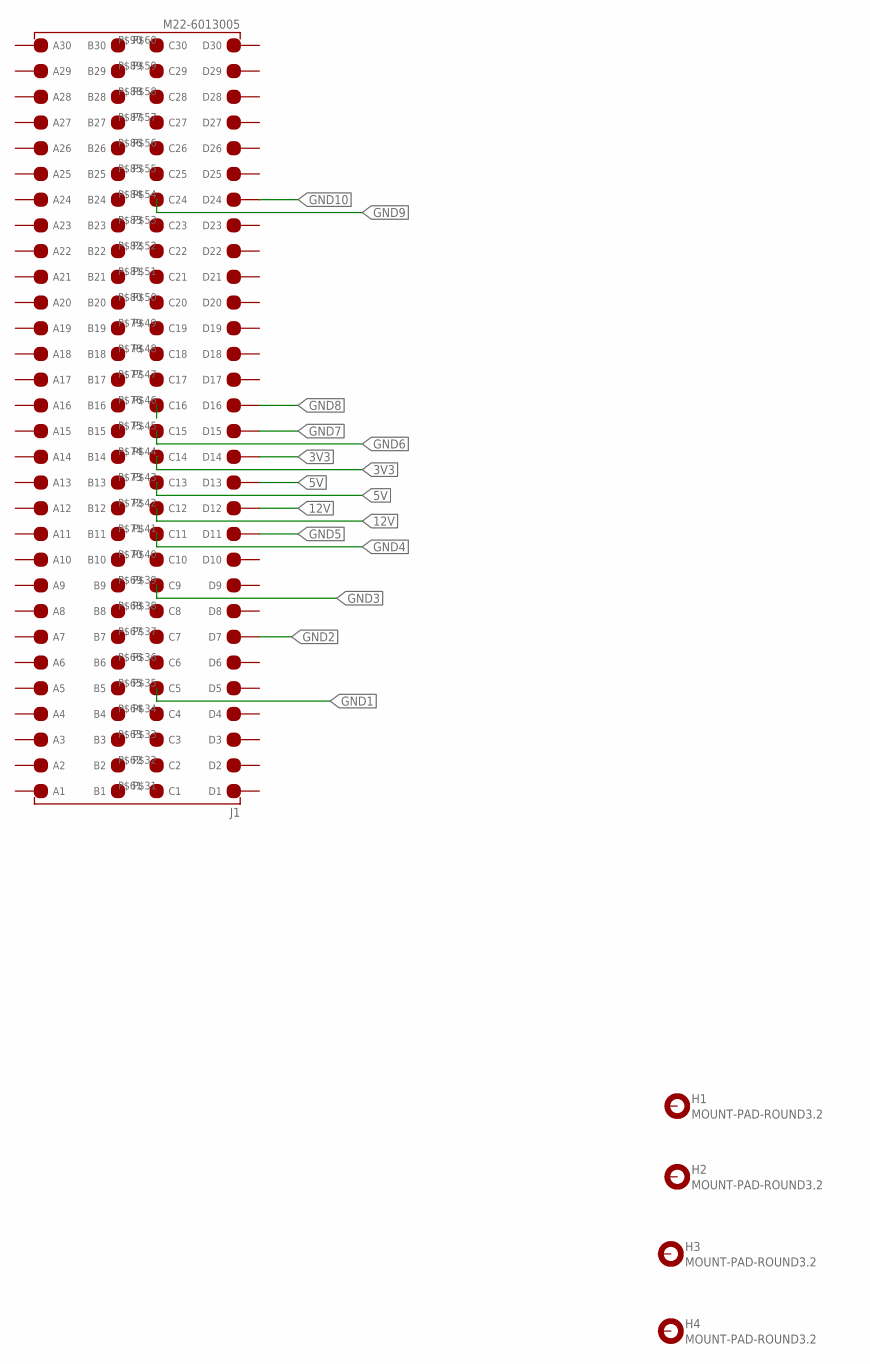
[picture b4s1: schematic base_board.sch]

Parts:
H1, H2, H3, H4: MOUNT-PAD-ROUND3.2; 3,2-PAD
J1: M22-6013005; RHDR120W55P200_4X30_6020X820X9

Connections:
3V3: J1.P$14 (D14), J1.P$44 (C14)
5V: J1.P$13 (D13), J1.P$43 (C13)
12V: J1.P$12 (D12), J1.P$42 (C12)
GND1: J1.P$35 (C5)
GND2: J1.P$7 (D7)
GND3: J1.P$39 (C9)
GND4: J1.P$41 (C11)
GND5: J1.P$11 (D11)
GND6: J1.P$45 (C15)
GND7: J1.P$15 (D15)
GND8: J1.P$16 (D16), J1.P$46 (C16)
GND9: J1.P$54 (C24)
GND10: J1.P$24 (D24)

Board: 2 copper layers, 5 parts (1 on the bottom side), 4 nets, no tracks yet.

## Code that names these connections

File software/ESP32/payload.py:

import machine
import time
import random
import demo_adc

class Payload():
    def __init__(self, sw=0, sw1=2, sw2=15, intr_out=32,  therm=13, unit=2, led=27, led1=14, led2=12, splash = False, sda=21,scl=22, addr=32):
        self.adc = demo_adc.temperature(pin=therm, unit=unit)
        self.sw = machine.Pin(sw, handler=self.switch, trigger=machine.Pin.IRQ_ANYEDGE)
        self.sw1 = machine.Pin(sw1, handler=self.switch1, trigger=machine.Pin.IRQ_ANYEDGE)
        self.sw2 = machine.Pin(sw2, handler=self.switch2, trigger=machine.Pin.IRQ_ANYEDGE)
        self.intr = machine.Pin(intr_out,   mode = machine.Pin.OUT, pull=machine.Pin.PULL_DOWN, value = 0)
        self.led = machine.Pin(led,   mode = machine.Pin.OUT, pull=machine.Pin.PULL_DOWN, value = 0)
        self.led1 = machine.Pin(led1, mode = machine.Pin.OUT, pull=machine.Pin.PULL_DOWN, value = 0)
        self.led2 = machine.Pin(led2, mode = machine.Pin.OUT, pull=machine.Pin.PULL_DOWN, value = 0)
        self.interupt = machine.Pin(33, handler=self.tidy_interupt, trigger=machine.Pin.IRQ_RISING)

        self.i2c = machine.I2C(1, mode=machine.I2C.SLAVE, sda=sda, scl=scl, slave_addr = addr)
        self.i2c.callback(self.i2c_cb, self.i2c.CBTYPE_ADDR | self.i2c.CBTYPE_TXDATA)
        
        if splash:
            self.splash()

    def led_increment(self):
        if self.led_count[2] == 1:
            self.led_count[2] = 0
            if self.led_count[1] == 1:
                self.led_count[1] = 0
                if self.led_count[0] == 1:
                    self.led_count[0] = 0
                else:
                    self.led_count[0] = 1
            else:
                self.led_count[1] = 1
        else:
            self.led_count[2] = 1

        self.led.value(self.led_count[2])
        self.led1.value(self.led_count[1])
        self.led2.value(self.led_count[0])
        
    def i2c_cb(self, res):
        cbtype = res[0] # i2c slave cllback type
        if cbtype == machine.I2C.CBTYPE_TXDATA:
            print("[I2C] Data sent to master: addr={}, len={}, ovf={}, data={}".format(res[1], res[2], res[3], res[4]))
        elif cbtype == machine.I2C.CBTYPE_ADDR:
            print("[I2C] Addres set: addr={}".format(res[1]))
            self.i2c.setdata(self.adc.get_temp_C(), 0)
        else:
            print("Unknown CB type, received: {}".format(res))

    def tidy_interupt(self, pin):
        self.intr.value(0)

    def switch(self,pin):
        print("Interupted SW")
        self.intr.value(1)
        #Set UART or I2C data

    def switch1(self,pin):
        print("Interupted SW1")
        self.intr.value(1)
        #Set UART or I2C data

    def switch2(self,pin):
        print("Interupted SW2")
        self.intr.value(1)
        #Set UART or I2C data

    def splash(self):
        for i in range(10):
            self.led.value(1)
            time.sleep(0.1)
            self.led.value(0)
            self.led1.value(1)
            time.sleep(0.1)
            self.led1.value(0)
            self.led2.value(1)
            time.sleep(0.1)
            self.led2.value(0)
        for i in range(3):
            self.led.value(1)
            self.led1.value(1)
            self.led2.value(1)
            time.sleep(0.1)
            self.led.value(0)
            self.led1.value(0)
            self.led2.value(0)
            time.sleep(0.1)

    def deinit(self):
        self.adc.deinit()
        self.i2c.deinit()

    def __del__(self):
        self.deinit()
        
